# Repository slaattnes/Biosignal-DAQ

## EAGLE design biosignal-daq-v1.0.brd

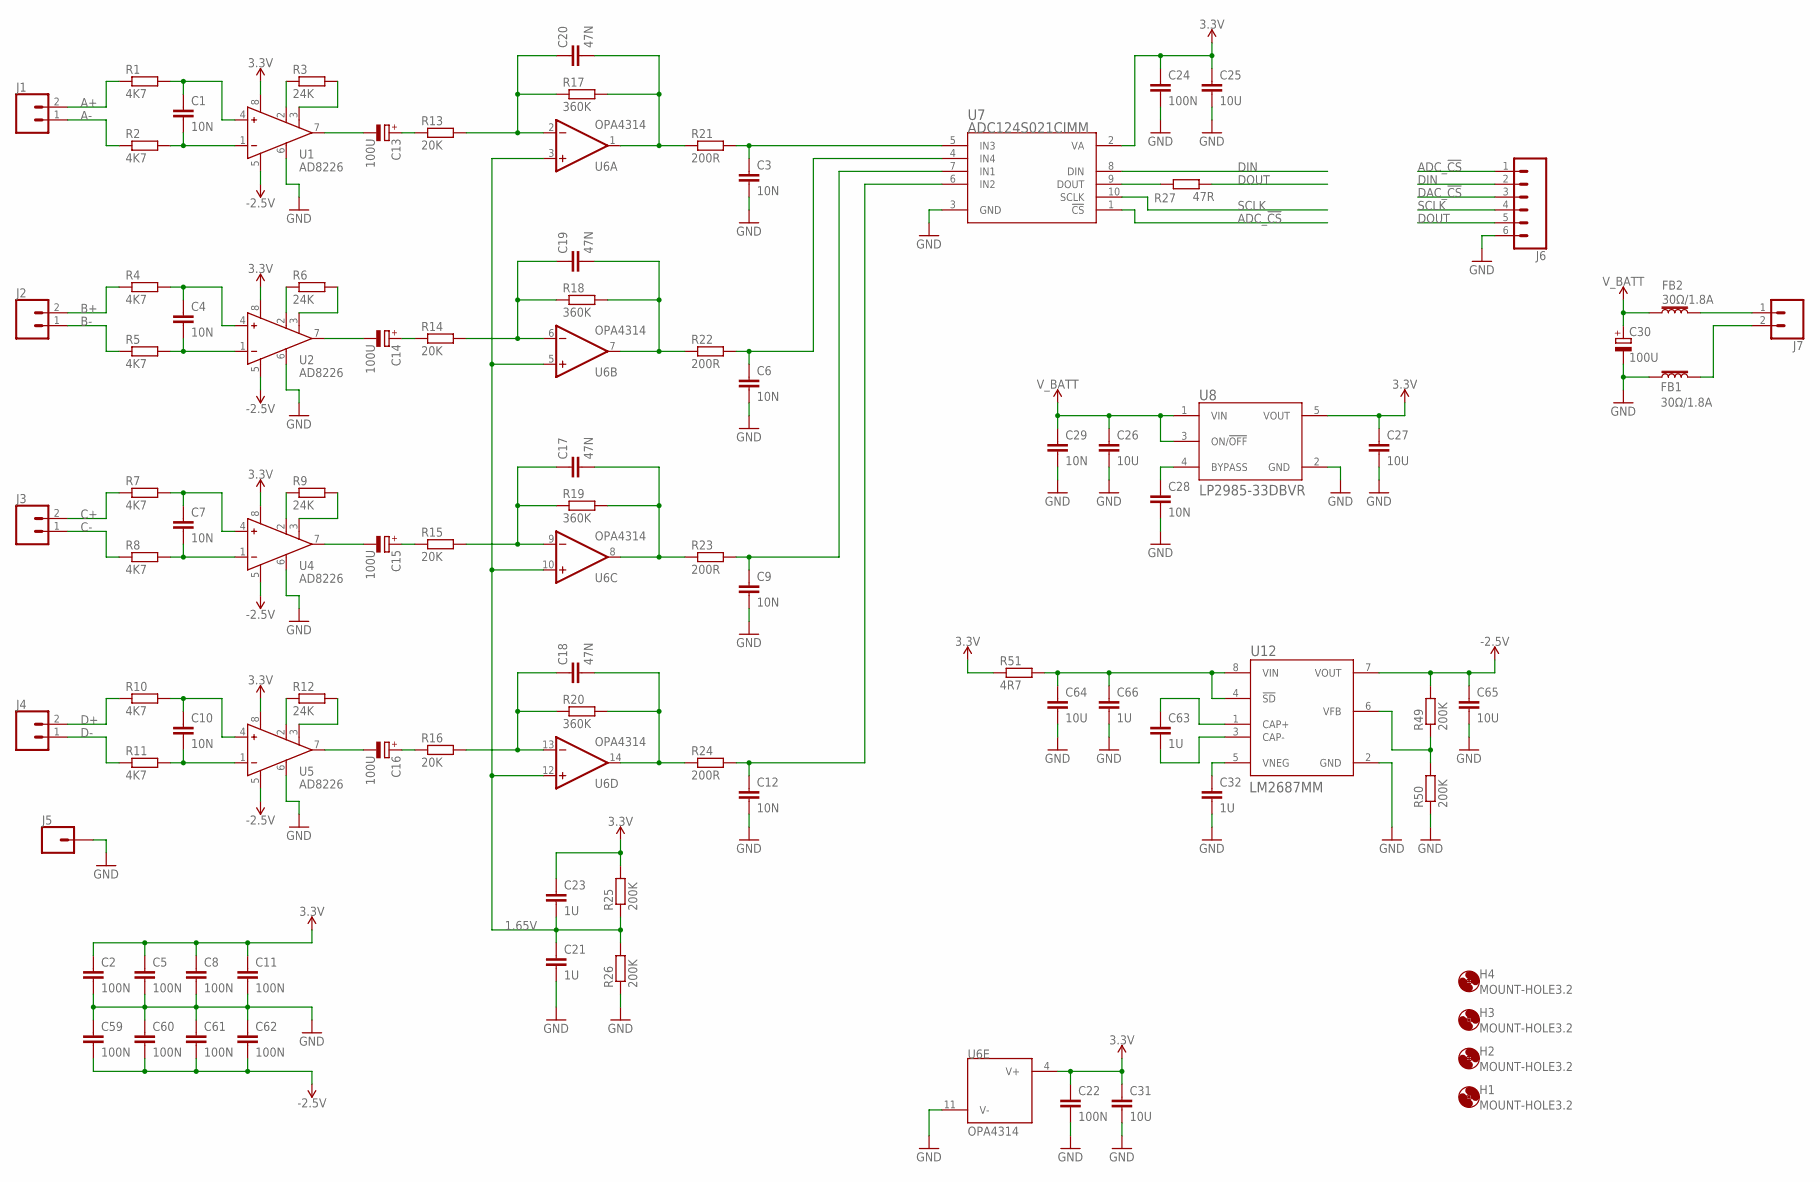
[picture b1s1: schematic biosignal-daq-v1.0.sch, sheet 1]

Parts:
C1, C3, C4, C6, C7, C9, C10, C12, C28, C29: 10N; CAPC160X80X91L36N
C2, C5, C8, C11, C22, C24, C59, C60, C61, C62: 100N; CAPC160X80X91L36N; RATING 10V; TOLERANCE 10%; MANUFACTURER_PART_NUMBER MC0603B104K100CT
C13, C14, C15, C16, C30: 100U; E2-5
C17, C18, C19, C20: 47N; CAPC200X125X80L50N
C21, C23, C32, C63, C66: 1U; CAPC160X80X91L36N
C25, C26, C27, C31, C64, C65: 10U; CAPC200X125X80L50N
FB1, FB2: 30Ω/1.8A; 0603
H1, H2, H3, H4: MOUNT-HOLE3.2; 3,2
J1, J2, J3, J4, J7: CONN_021X02_NO_SILK; 1X02_NO_SILK
J5: CONN_01; 1X01
J6: CONN_06NO_SILK_NO_POP; 1X06_NO_SILK
R1, R2, R4: 4K7; RESC160X80X55L25N; RATING 100mW; TOLERANCE 1%
R3: 24K; RESC160X80X55L25N; RATING 100mW; TOLERANCE 1%
R5, R7, R8, R10, R11: 4K7; RESC160X80X55L25N
R6, R9, R12: 24K; RESC160X80X55L25N
R13, R14, R15, R16: 20K; RESC160X80X55L25N
R17, R18, R19, R20: 360K; RESC160X80X55L25N
R21, R22, R23, R24: 200R; RESC160X80X55L25N
R25, R26, R49, R50: 200K; RESC160X80X55L25N
R27: 47R; RESC160X80X55L25N
R51: 4R7; RESC160X80X55L25N
U1, U2, U4, U5: AD8226; SOP8P65_300X490X95L60X32N
U6: OPA4314; PW14
U7: ADC124S021CIMM; MUB10A
U8: LP2985-33DBVR; DBV5
U12: LM2687MM; MUA08A

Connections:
1.65V: C21.1, C23.2, R25.1, R26.2, U6.3 (+IN), U6.5 (+IN), U6.10 (+IN), U6.12 (+IN)
3.3V: C2.1, C5.1, C8.1, C11.1, C22.1, C23.1, C24.1, C25.1, C27.1, C31.1, R25.2, R51.1, U1.8 (+VS), U2.8 (+VS), U4.8 (+VS), U5.8 (+VS), U6.4 (V+), U7.2 (VA), U8.5 (VOUT); also elsewhere on the board
-2.5V: C59.2, C60.2, C61.2, C62.2, C65.1, R49.2, U1.5 (-VS), U2.5 (-VS), U4.5 (-VS), U5.5 (-VS), U12.7 (VOUT)
A+: J1.2, R1.1
A-: J1.1, R2.1
ADC_!CS: J6.1, U7.1 (!CS)
B+: J2.2, R4.1
B-: J2.1, R5.1
C+: J3.2, R7.1
C-: J3.1, R8.1
D+: J4.2, R10.1
D-: J4.1, R11.1
DAC_!CS: J6.3; also elsewhere on the board
DIN: J6.2, U7.8 (DIN); also elsewhere on the board
DOUT: J6.5, R27.2
GND: C2.2, C3.2, C5.2, C6.2, C8.2, C9.2, C11.2, C12.2, C21.2, C22.2, C24.2, C25.2, C26.2, C27.2, C28.2, C29.2, C30.-, C31.2, C32.2, C59.1, C60.1, C61.1, C62.1, C64.2, C65.2, C66.2, FB1.1, J5.1, J6.6, R26.1, R50.1, U1.6 (REF), U2.6 (REF), U4.6 (REF), U5.6 (REF), U6.11 (V-), U7.3 (GND), U8.2 (GND), U12.2 (GND); also elsewhere on the board
unnamed: C1.1, R1.2, U1.4 (IN+)
unnamed: C1.2, R2.2, U1.1 (IN-)
unnamed: R3.1, U1.2 (RG)
unnamed: R3.2, U1.3 (RG)
unnamed: C4.1, R4.2, U2.4 (IN+)
unnamed: C4.2, R5.2, U2.1 (IN-)
unnamed: R6.1, U2.2 (RG)
unnamed: R6.2, U2.3 (RG)
unnamed: C7.1, R7.2, U4.4 (IN+)
unnamed: C7.2, R8.2, U4.1 (IN-)
unnamed: R9.1, U4.2 (RG)
unnamed: R9.2, U4.3 (RG)
unnamed: C10.1, R10.2, U5.4 (IN+)
unnamed: C10.2, R11.2, U5.1 (IN-)
unnamed: R12.1, U5.2 (RG)
unnamed: R12.2, U5.3 (RG)
unnamed: C13.-, U1.7 (VOUT)
unnamed: C13.+, R13.1
unnamed: C14.-, U2.7 (VOUT)
unnamed: C14.+, R14.1
unnamed: C15.-, U4.7 (VOUT)
unnamed: C15.+, R15.1
unnamed: C16.-, U5.7 (VOUT)
unnamed: C16.+, R16.1
unnamed: C6.1, R22.2, U7.4 (IN4)
unnamed: C19.1, R14.2, R18.1, U6.6 (-IN)
unnamed: C18.1, R16.2, R20.1, U6.13 (-IN)
unnamed: C18.2, R20.2, R24.1, U6.14 (OUT)
unnamed: C17.1, R15.2, R19.1, U6.9 (-IN)
unnamed: C17.2, R19.2, R23.1, U6.8 (OUT)
unnamed: C19.2, R18.2, R22.1, U6.7 (OUT)
unnamed: C20.1, R13.2, R17.1, U6.2 (-IN)
unnamed: C20.2, R17.2, R21.1, U6.1 (OUT)
unnamed: C9.1, R23.2, U7.7 (IN1)
unnamed: C12.1, R24.2, U7.6 (IN2)
unnamed: C3.1, R21.2, U7.5 (IN3)
unnamed: R27.1, U7.9 (DOUT)
unnamed: FB2.2, J7.1
unnamed: FB1.2, J7.2
unnamed: C28.1, U8.4 (BYPASS)
unnamed: R49.1, R50.2, U12.6 (VFB)
unnamed: C64.1, C66.1, R51.2, U12.4 (!SD), U12.8 (VIN)
unnamed: C63.1, U12.1 (CAP+)
unnamed: C63.2, U12.3 (CAP-)
unnamed: C32.1, U12.5 (VNEG)
SCLK: J6.4, U7.10 (SCLK); also elsewhere on the board
V_BATT: C26.1, C29.1, C30.+, FB2.1, U8.1 (VIN), U8.3 (ON/!OFF)

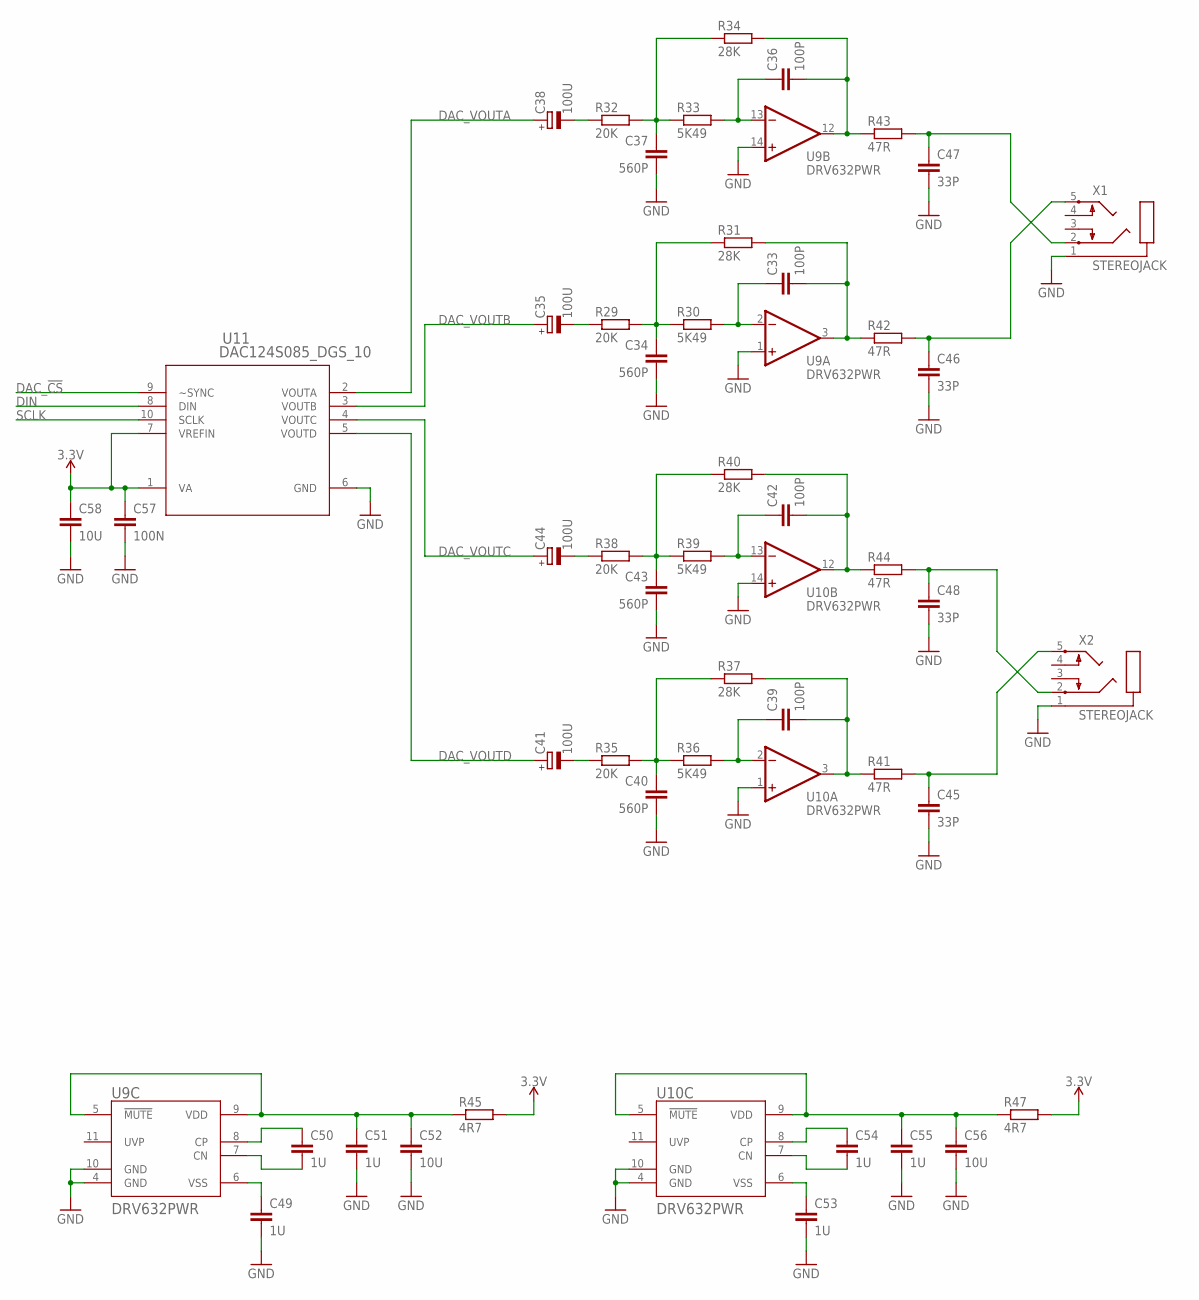
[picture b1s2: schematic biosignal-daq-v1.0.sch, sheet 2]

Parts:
C33, C36, C39, C42: 100P; CAPC160X80X91L36N
C34, C37, C40, C43: 560P; CAPC160X80X91L36N
C35, C38, C41, C44: 100U; E2-5
C45, C46, C47, C48: 33P; CAPC160X80X91L36N
C49, C50, C51, C53, C54, C55: 1U; CAPC160X80X91L36N
C52, C56, C58: 10U; CAPC200X125X80L50N
C57: 100N; CAPC160X80X91L36N
R29, R32, R35, R38: 20K; RESC160X80X55L25N
R30, R33, R36, R39: 5K49; RESC160X80X55L25N
R31, R34, R37, R40: 28K; RESC160X80X55L25N
R41, R42, R43, R44: 47R; RESC160X80X55L25N
R45, R47: 4R7; RESC160X80X55L25N
U9, U10: DRV632PWR; PW14
U11: DAC124S085_DGS_10; MUB10A
X1, X2: STEREOJACK; STX3100

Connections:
3.3V: C57.1, C58.1, R45.2, R47.2, U11.1 (VA), U11.7 (VREFIN); also elsewhere on the board
DAC_!CS: U11.9 (~SYNC); also elsewhere on the board
DAC_VOUTA: C38.+, U11.2 (VOUTA)
DAC_VOUTB: C35.+, U11.3 (VOUTB)
DAC_VOUTC: C44.+, U11.4 (VOUTC)
DAC_VOUTD: C41.+, U11.5 (VOUTD)
DIN: U11.8 (DIN); also elsewhere on the board
GND: C34.2, C37.2, C40.2, C43.2, C45.2, C46.2, C47.2, C48.2, C49.2, C51.2, C52.2, C53.2, C55.2, C56.2, C57.2, C58.2, U9.1 (+IN), U9.4 (GND), U9.10 (GND), U9.14 (+IN), U10.1 (+IN), U10.4 (GND), U10.10 (GND), U10.14 (+IN), U11.6 (GND), X1.1, X2.1; also elsewhere on the board
unnamed: C47.1, R43.2, X1.2
unnamed: C34.1, R29.2, R30.1, R31.1
unnamed: C33.1, R30.2, U9.2 (-IN)
unnamed: C33.2, R31.2, R42.1, U9.3 (OUT)
unnamed: C35.-, R29.1
unnamed: C37.1, R32.2, R33.1, R34.1
unnamed: C36.1, R33.2, U9.13 (-IN)
unnamed: C36.2, R34.2, R43.1, U9.12 (OUT)
unnamed: C38.-, R32.1
unnamed: C40.1, R35.2, R36.1, R37.1
unnamed: C39.1, R36.2, U10.2 (-IN)
unnamed: C39.2, R37.2, R41.1, U10.3 (OUT)
unnamed: C41.-, R35.1
unnamed: C43.1, R38.2, R39.1, R40.1
unnamed: C42.1, R39.2, U10.13 (-IN)
unnamed: C42.2, R40.2, R44.1, U10.12 (OUT)
unnamed: C44.-, R38.1
unnamed: C45.1, R41.2, X2.5
unnamed: C46.1, R42.2, X1.5
unnamed: C48.1, R44.2, X2.2
unnamed: C50.1, U9.8 (CP)
unnamed: C50.2, U9.7 (CN)
unnamed: C49.1, U9.6 (VSS)
unnamed: C51.1, C52.1, R45.1, U9.5 (!MUTE), U9.9 (VDD)
unnamed: C54.1, U10.8 (CP)
unnamed: C54.2, U10.7 (CN)
unnamed: C53.1, U10.6 (VSS)
unnamed: C55.1, C56.1, R47.1, U10.5 (!MUTE), U10.9 (VDD)
SCLK: U11.10 (SCLK); also elsewhere on the board

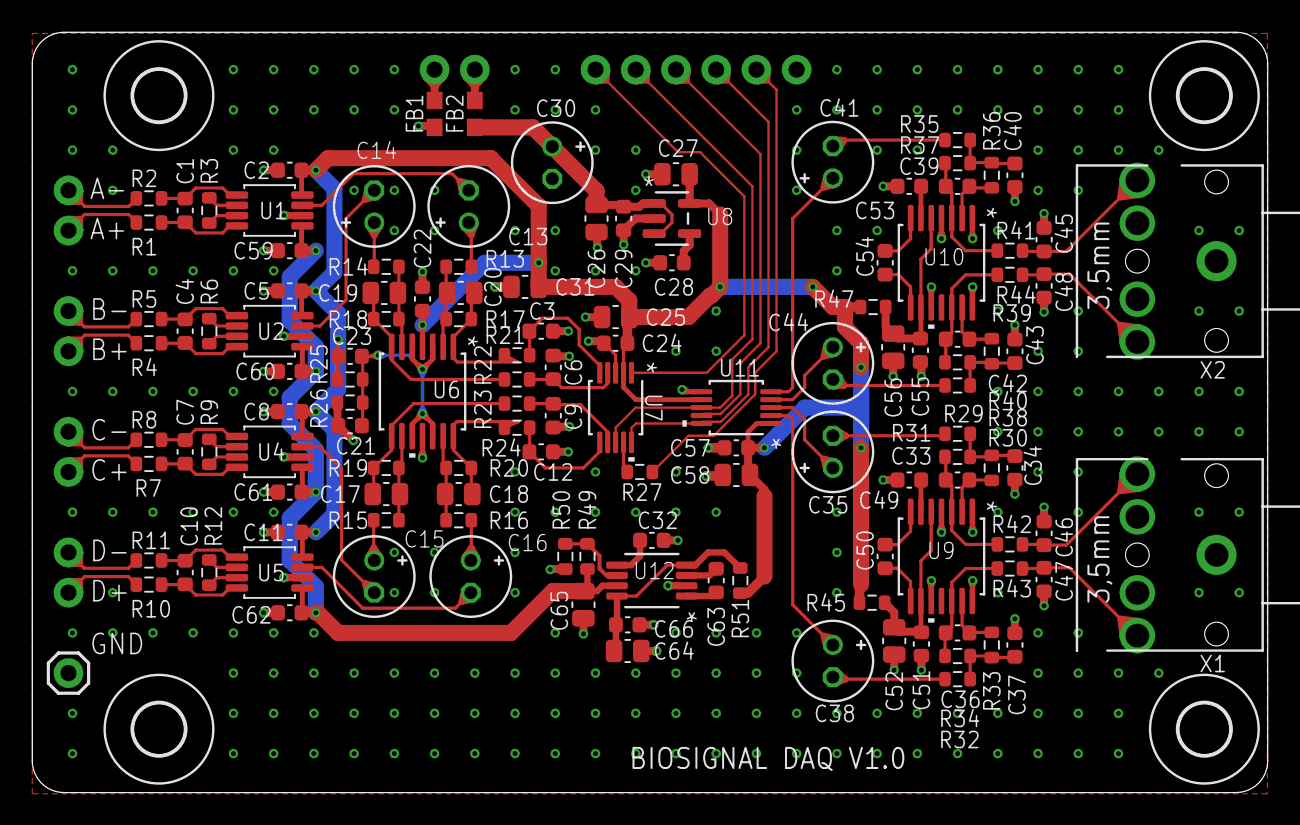
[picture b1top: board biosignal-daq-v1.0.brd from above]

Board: 2 copper layers, 78.0 x 48.0 mm, 140 parts (0 on the bottom side), 95 nets.

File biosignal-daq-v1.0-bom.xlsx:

Qty | Value | Device | Package | Parts | MANUFACTURER_PART_NUMBER | RATING | TECHNOLOGY | TOLERANCE | VENDOR
10 | 10N | C0603 | CAPC160X80X91L36N | C1, C3, C4, C6, C7, C9, C10, C12, C28, C29 | MC0603B103K101CT | 100 V | X7R | 0.1 | Multicomp
9 | 100U | CPOL-EUE2-5 | E2-5 | C13, C14, C15, C16, C30, C35, C38, C41, C44 | UKW1C101MDD | 16 V |  | 0.2 | Nichicon
4 | 47N | C0805 | CAPC200X125X80L50N | C17, C18, C19, C20 | C0805C473K3GAC7800 | 25 V | C0G | 0.1 | KEMET
11 | 100N | C0603 | CAPC160X80X91L36N | C2, C5, C8, C11, C22, C24, C57, C59, C60, C61, C62 | MC0603B104K100CT | 10V | X7R | 0.1 | Multicomp
11 | 1U | C0603 | CAPC160X80X91L36N | C21, C23, C32, C49, C50, C51, C53, C54, C55, C63, C66 | 885012106010 | 10 V | X5R | 0.2 | Würth
9 | 10U | C0805 | CAPC200X125X80L50N | C25, C26, C27, C31, C52, C56, C58, C64, C65 | MCTT21X106M6R3CT | 6.3 V | X5R | 0.2 | Multicomp
4 | 100P | C0603 | CAPC160X80X91L36N | C33, C36, C39, C42 | MC0603N101J101CT | 100 V | C0G | 0.05 | Multicomp
4 | 560P | C0603 | CAPC160X80X91L36N | C34, C37, C40, C43 | 0603N561J500CT | 50 V | C0G | 0.05 | Walsin
4 | 33P | C0603 | CAPC160X80X91L36N | C45, C46, C47, C48 | 0603N330J250CT | 25 V | C0G | 0.05 | Walsin
2 | 30Œ©/1.8A | FERRITE_BEAD-0603 | 603 | FB1, FB2 | BLM18AG102SN1D |  |  |  | Murata
8 | 4K7 | R0603 | RESC160X80X55L25N | R1, R2, R4, R5, R7, R8, R10, R11 | MCWR06X4701FTL | 100mW |  | 0.01 | Multicomp
8 | 20K | R0603 | RESC160X80X55L25N | R13, R14, R15, R16, R29, R32, R35, R38 | MCWR06X2002FTL | 100 mW |  | 0.01 | Multicomp
4 | 360K | R0603 | RESC160X80X55L25N | R17, R18, R19, R20 | MCWR06X3603FTL | 100 mW |  | 0.01 | Multicomp
4 | 200R | R0603 | RESC160X80X55L25N | R21, R22, R23, R24 | MCWR06X2000FTL | 100 mW |  | 0.01 | Multicomp
4 | 200K | R0603 | RESC160X80X55L25N | R25, R26, R49, R50 | MCMR06X2003FTL | 100 mW |  | 0.01 | Multicomp
5 | 47R | R0603 | RESC160X80X55L25N | R27, R41, R42, R43, R44 | MCWR06W47R0FTL | 100 mW |  | 0.01 | Multicomp
4 | 24K | R0603 | RESC160X80X55L25N | R3, R6, R9, R12 | MCWR06X2402FTL | 100 mW |  | 0.01 | Multicomp
4 | 5K49 | R0603 | RESC160X80X55L25N | R30, R33, R36, R39 | MCMR06X5491FTL | 100 mW |  | 0.01 | Multicomp
4 | 28K | R0603 | RESC160X80X55L25N | R31, R34, R37, R40 | MCMR06X2802FTL | 100 mW |  | 0.01 | Multicomp
3 | 4R7 | R0603 | RESC160X80X55L25N | R45, R47, R51 | MCWR06W4R70FTL | 100 mW |  | 0.01 | Multicomp
4 | AD8226 | AD8226 | SOP8P65_300X490X95L60X32N | U1, U2, U4, U5 | AD8226ARMZ |  |  |  | Analog Devices
1 | DAC124S085_DGS_10 | DAC124S085_DGS_10 | MUB10A | U11 | DAC124S085_DGS_10 |  |  |  | Texas Instruments
1 | LM2687MM | LM2687MM | MUA08A | U12 | LM2687MM |  |  |  | Texas Instruments
1 | OPA4314 | OPA4314 | PW14 | U6 | OPA4314AIPWR |  |  |  | Texas Instruments
1 | ADC124S021CIMM | ADC124S021CIMM | MUB10A | U7 | ADC124S021CIMM |  |  |  | Texas Instruments
1 | LP2985-33DBVR | LP2985-33DBVR | DBV5 | U8 | LP298533DBVR |  |  |  | Texas Instruments
2 | DRV632PWR | DRV632PWR | PW14 | U9, U10 | DRV632PWR |  |  |  | Texas Instruments
2 | STEREOJACK | STEREOJACK | STX3100 | X1, X2 | SJ1-3555NG |  |  |  | CUI
129

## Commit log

2019-06-18 Typo of Manufacturer Part Number

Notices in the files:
parts and their libraries:
SparkFun-Connectors: Licensing: Creative Commons ShareAlike 4.0 International - https://creativecommons.org/licenses/by-sa/4.0
